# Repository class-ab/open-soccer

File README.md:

contains all the PCBs, code and general shared documentation used in the creation of Mindstormers' open soccer robot/s (2026+)

CAD: https://cad.onshape.com/documents/fc0a5e085ca7f56b4458a98d/w/3d7a112d05c35eb898b84bfe/e/c55f60db607fb82f3faf3afa?renderMode=0&uiState=6a391f8bb5ef6c9da8a4baea

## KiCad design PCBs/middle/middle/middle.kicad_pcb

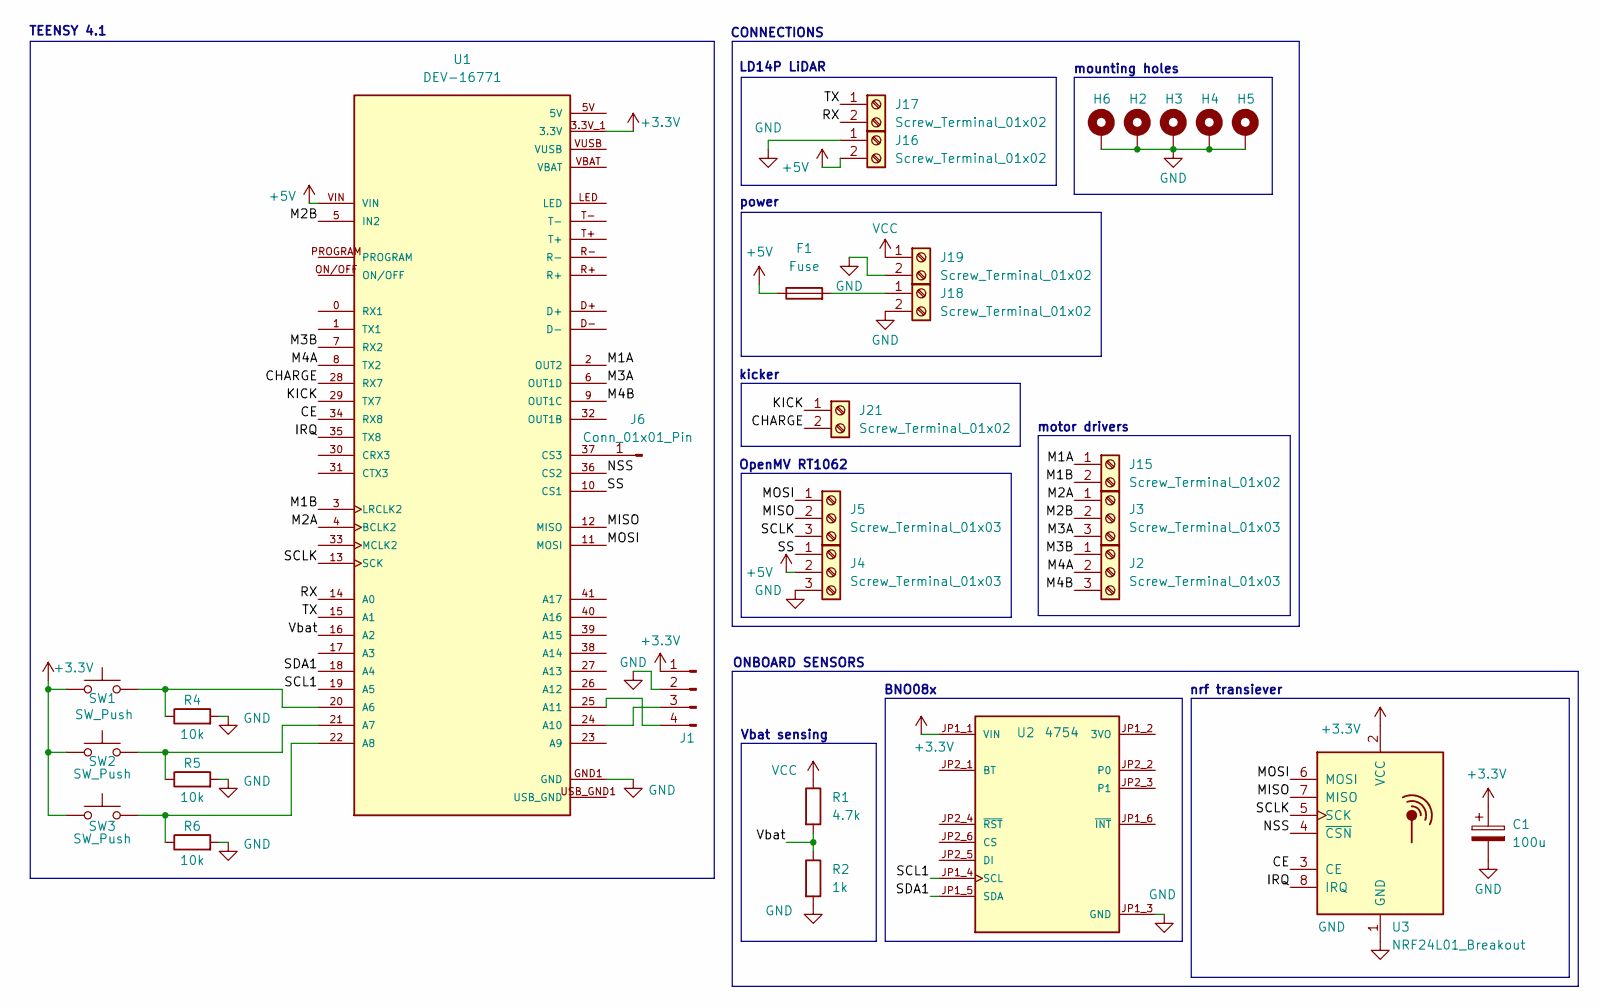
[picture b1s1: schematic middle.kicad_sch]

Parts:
C1: 100u; CP_Radial_D6.3mm_P2.50mm
F1: Fuse; Fuseholder_Clip-5x20mm_Littelfuse_520_Inline_P20.50x5.80mm_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
H2, H3, H4, H5, H6: MountingHole_Pad; MountingHole_3.2mm_M3_DIN965_Pad
J1: Conn_01x04_Pin; PinSocket_1x04_P2.54mm_Vertical
J2, J3, J4, J5: Screw_Terminal_01x03; TerminalBlock_Phoenix_MKDS-1,5-3_1x03_P5.00mm_Horizontal
J6: Conn_01x01_Pin; PinHeader_1x01_P2.54mm_Vertical
J15, J16, J17, J18, J19, J21: Screw_Terminal_01x02; TerminalBlock_Phoenix_MKDS-1,5-2_1x02_P5.00mm_Horizontal
R1: 4.7k; R_Axial_DIN0207_L6.3mm_D2.5mm_P10.16mm_Horizontal
R2: 1k; R_Axial_DIN0207_L6.3mm_D2.5mm_P10.16mm_Horizontal
R4, R5, R6: 10k; R_Axial_DIN0204_L3.6mm_D1.6mm_P5.08mm_Horizontal
SW1, SW2, SW3: SW_Push; SW_PUSH_6mm_H5mm
U1: DEV-16771; MODULE_DEV-16771; PARTREV 4.1
U2: 4754; MODULE_4754; PARTREV 2021-03-16
U3: NRF24L01_Breakout; nRF24L01_Breakout

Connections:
+3.3V: C1.1, J1.1, SW1.1, SW2.1, SW3.1, U1.3.3V_1 (3.3V), U1.3.3V_2 (3.3V), U1.3.3V_3 (3.3V), U2.JP1_1 (VIN), U3.2 (VCC)
+5V: F1.1, J4.2, J16.2, U1.VIN
/CE: U1.34 (RX8), U3.3 (CE)
/CHARGE: J21.2, U1.28 (RX7)
/IRQ: U1.35 (TX8), U3.8 (IRQ)
/KICK: J21.1, U1.29 (TX7)
/M1A: J15.1, U1.2 (OUT2)
/M1B: J15.2, U1.3 (LRCLK2)
/M2A: J3.1, U1.4 (BCLK2)
/M2B: J3.2, U1.5 (IN2)
/M3A: J3.3, U1.6 (OUT1D)
/M3B: J2.1, U1.7 (RX2)
/M4A: J2.2, U1.8 (TX2)
/M4B: J2.3, U1.9 (OUT1C)
/MISO: J5.2, U1.12 (MISO), U3.7 (MISO)
/MOSI: J5.1, U1.11 (MOSI), U3.6 (MOSI)
/NSS: U1.36 (CS2), U3.4 (~CSN)
/RX: J17.2, U1.14 (A0)
/SCL1: U1.19 (A5), U2.JP1_4 (SCL)
/SCLK: J5.3, U1.13 (SCK), U3.5 (SCK)
/SDA1: U1.18 (A4), U2.JP1_5 (SDA)
/SS: J4.1, U1.10 (CS1)
/TX: J17.1, U1.15 (A1)
/Vbat: R1.2, R2.1, U1.16 (A2)
GND: C1.2, H2.1 (1_1), H3.1 (1_1), H4.1 (1_1), H5.1 (1_1), H6.1 (1_1), J1.2, J4.3, J16.1, J18.2, J19.2, R2.2, R4.2, R5.2, R6.2, U1.GND1 (GND), U1.GND2 (GND), U1.GND3 (GND), U1.GND4 (GND), U1.GND5 (GND), U2.JP1_3 (GND), U3.1 (GND)
unnamed: J1.3, U1.24 (A10)
unnamed: J1.4, U1.25 (A11)
unnamed: J6.1 (Pin_1_1), U1.37 (CS3)
unnamed: F1.2, J18.1
unnamed: R4.1, SW1.2, U1.20 (A6)
unnamed: R5.1, SW2.2, U1.21 (A7)
unnamed: R6.1, SW3.2, U1.22 (A8)
USB_GND: U1.USB_GND1 (USB_GND), U1.USB_GND2 (USB_GND)
VCC: J19.1, R1.1

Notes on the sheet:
BNO08x
power
LD14P LiDAR
mounting holes
CONNECTIONS
OpenMV RT1062
nrf transiever
TEENSY 4.1
motor drivers
kicker
Vbat sensing
ONBOARD SENSORS

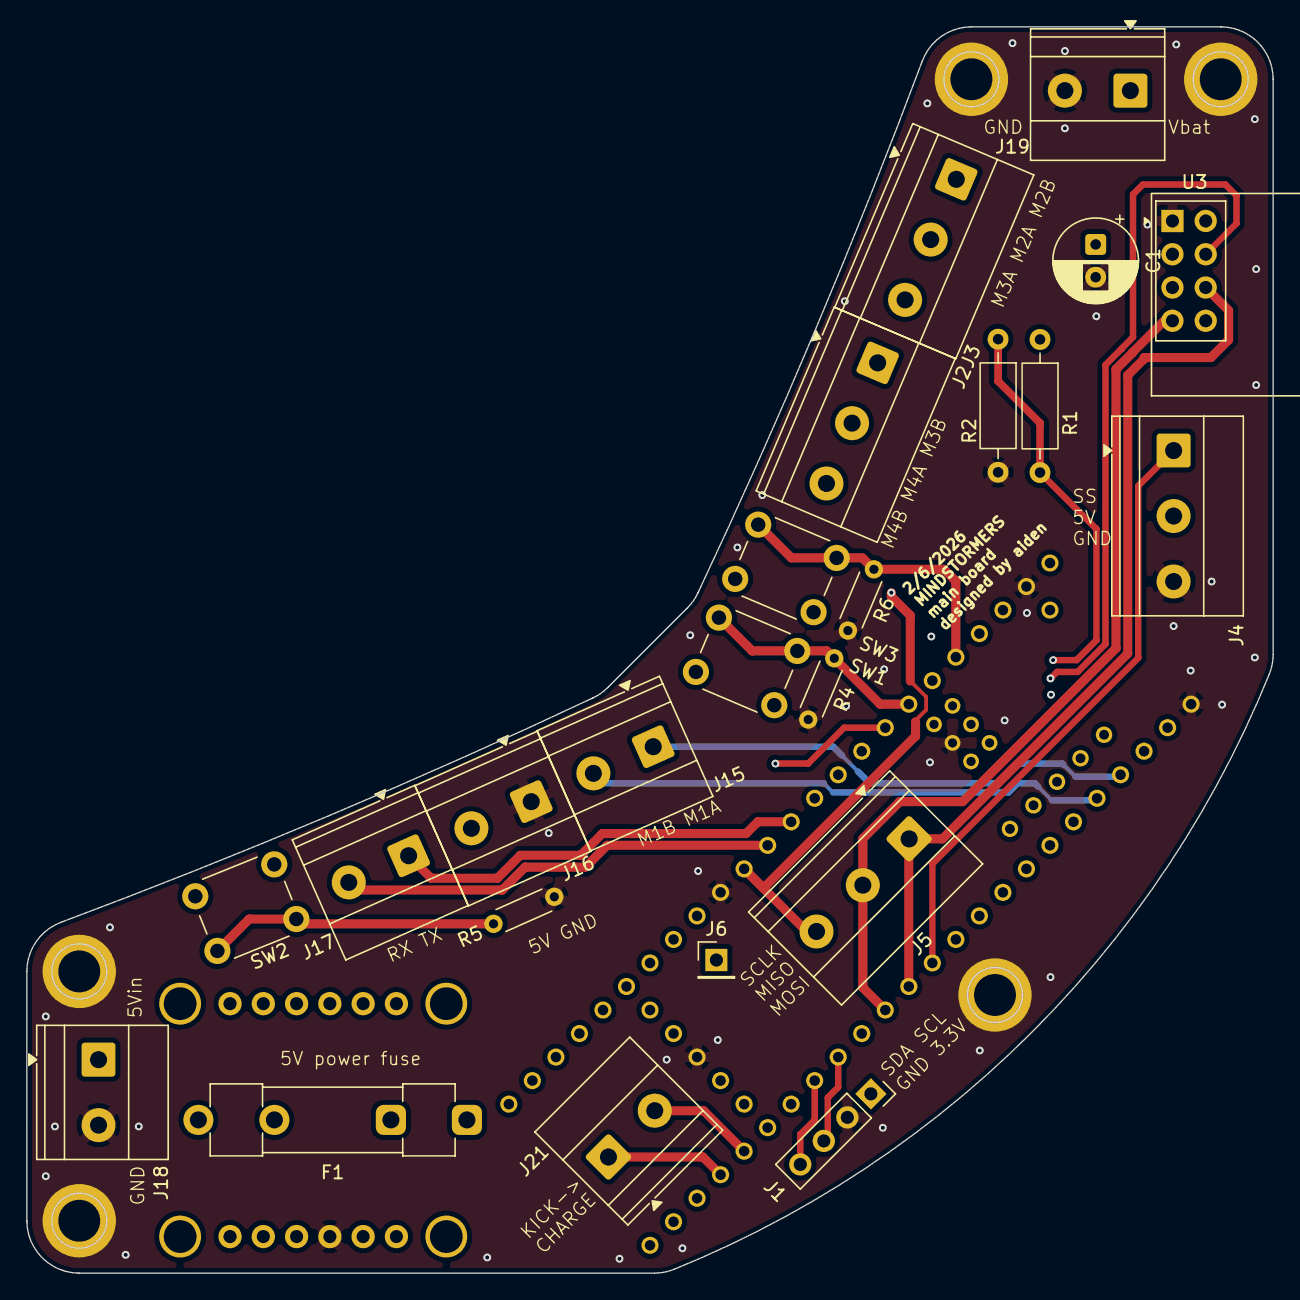
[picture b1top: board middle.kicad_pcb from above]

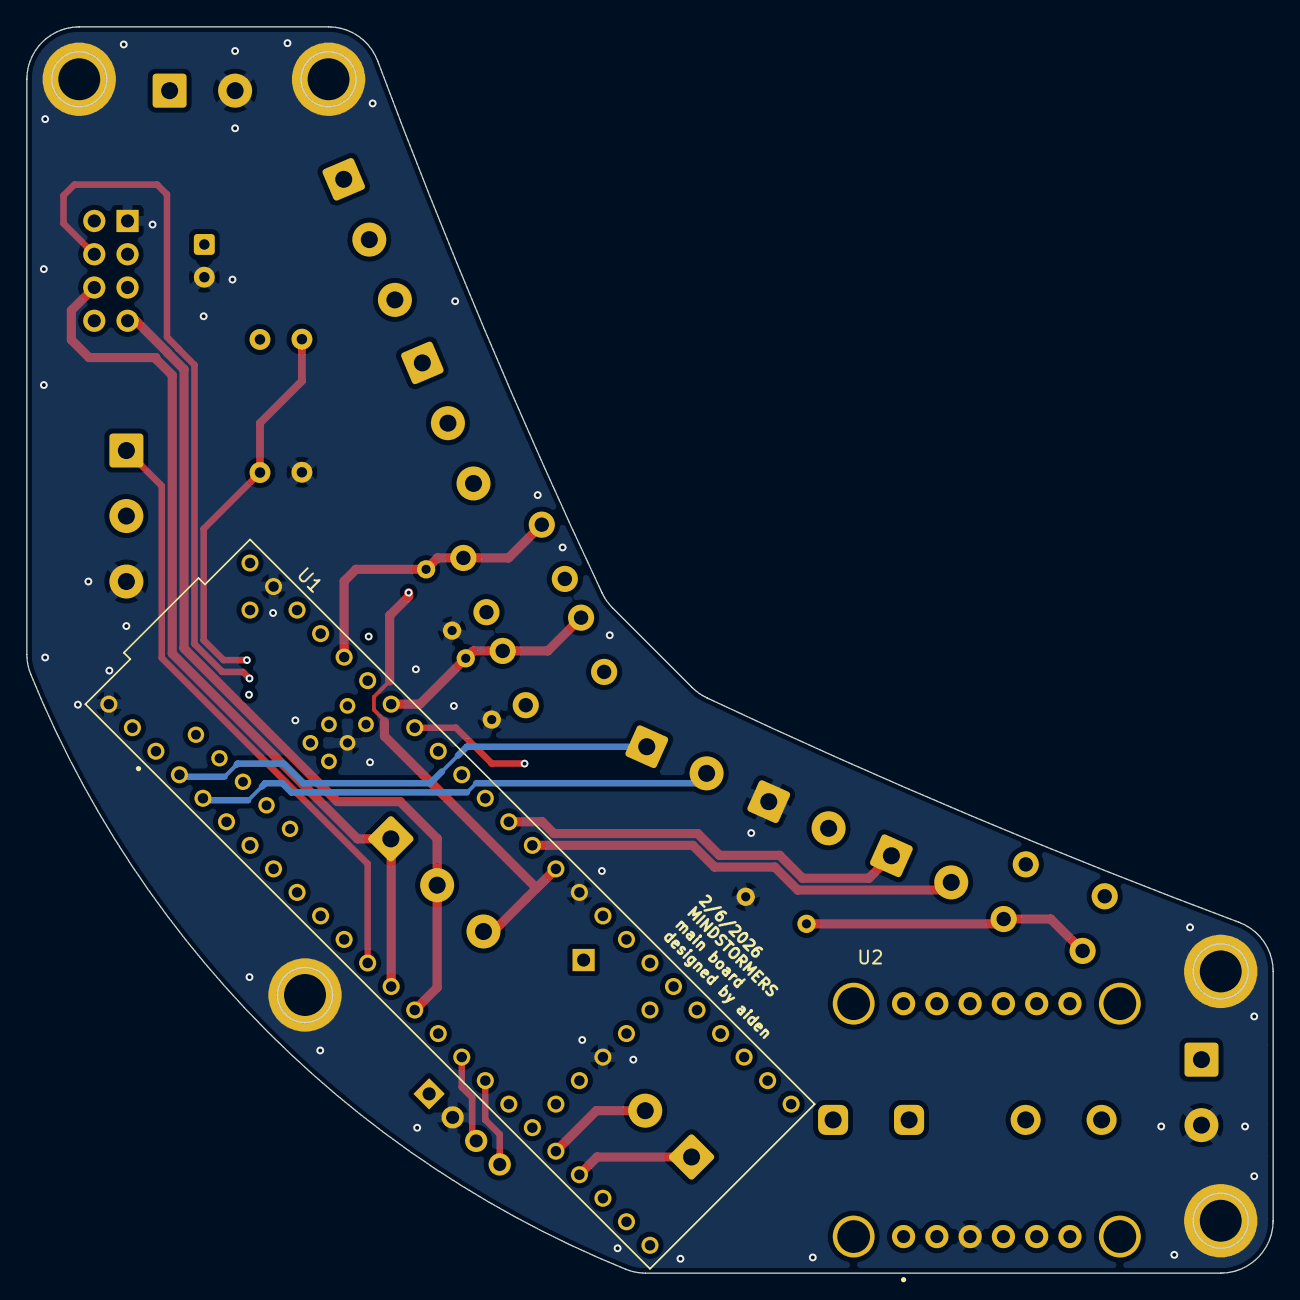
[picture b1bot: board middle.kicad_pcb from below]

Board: 4 copper layers, 95.1 x 95.1 mm, 30 parts (2 on the bottom side), 34 nets.

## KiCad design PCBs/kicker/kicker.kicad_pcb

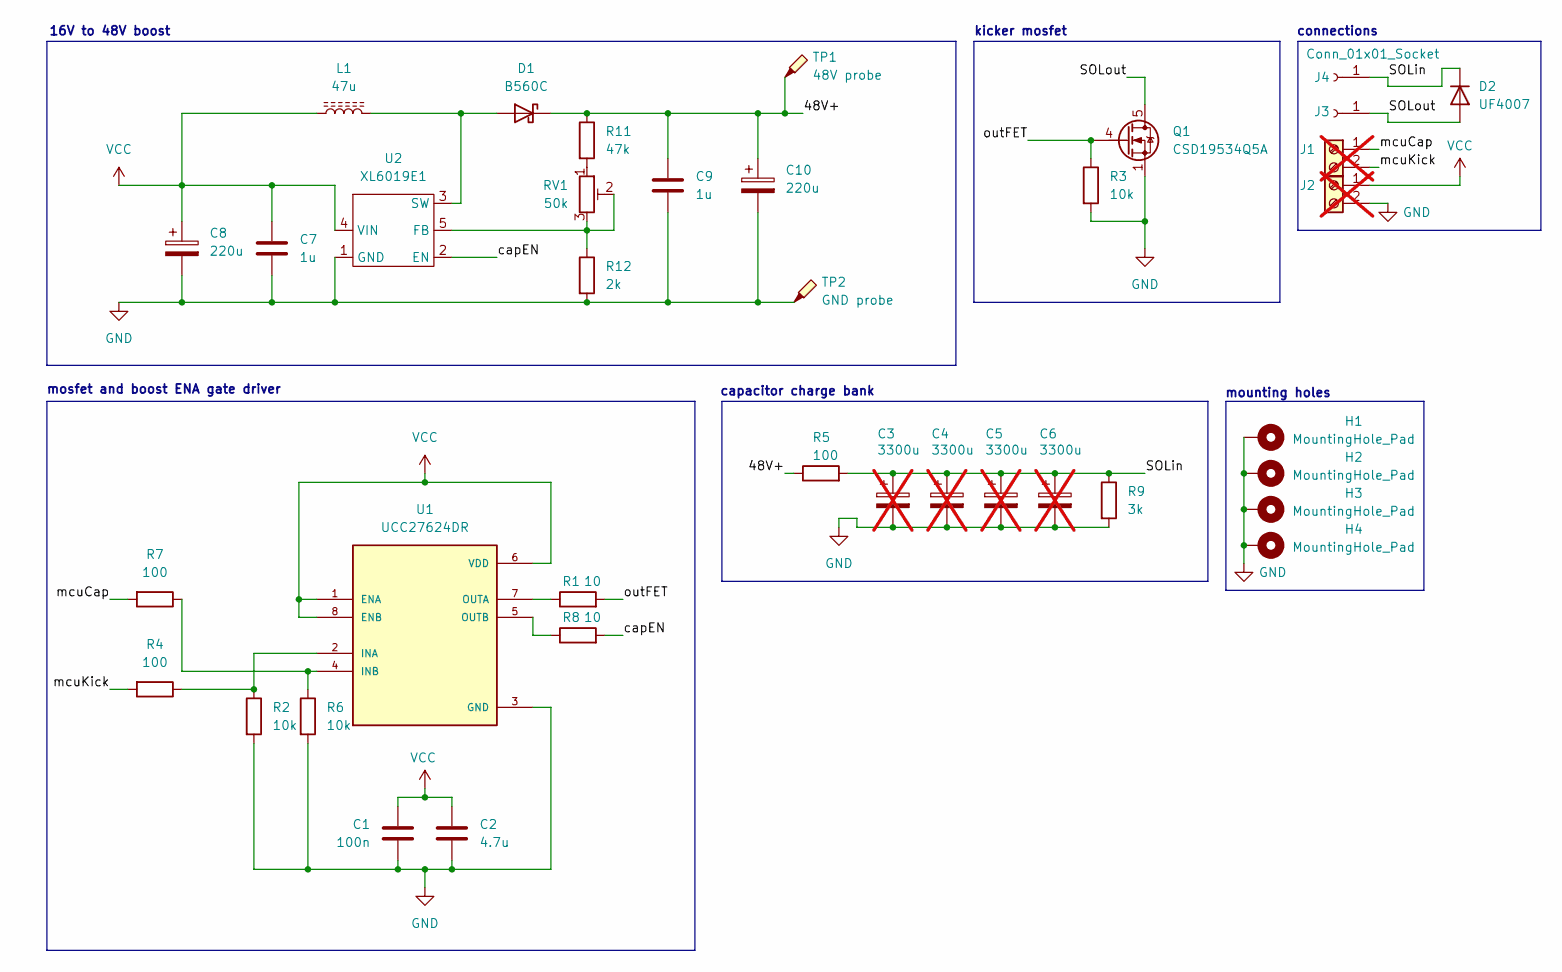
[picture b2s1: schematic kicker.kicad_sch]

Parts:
C1: 100n; C_1206_3216Metric
C2: 4.7u; C_1206_3216Metric
C3, C4, C5, C6: 3300u; CP_Radial_D18.0mm_P7.50mm; not fitted
C7, C9: 1u; C_1206_3216Metric
C8, C10: 220u; CP_Elec_10x10.5
D1: B560C; DO-214AB
D2: UF4007; D_DO-41_SOD81_P10.16mm_Horizontal
H1, H2, H3, H4: MountingHole_Pad; MountingHole_3.2mm_M3_DIN965_Pad
J1, J2: Screw_Terminal_01x02; TerminalBlock_Phoenix_MKDS-1,5-2_1x02_P5.00mm_Horizontal; not fitted
J3, J4: Conn_01x01_Socket; SolderWirePad_1x01_SMD_3x6mm
L1: 47u; L_Sunlord_MWSA1206S-470
Q1: CSD19534Q5A; TDSON-8-1
R1, R8: 10; R_0805_2012Metric
R2, R3, R6: 10k; R_0603_1608Metric
R4, R7: 100; R_0603_1608Metric
R5: 100; TO-263-2
R9: 3k; R_2512_6332Metric
R11: 47k; R_0603_1608Metric
R12: 2k; R_0603_1608Metric
RV1: 50k; Potentiometer_Bourns_3296W_Vertical
TP1: 48V probe; TestPoint_THTPad_1.5x1.5mm_Drill0.7mm
TP2: GND probe; TestPoint_THTPad_1.5x1.5mm_Drill0.7mm
U1: UCC27624DR; SOIC-8_3.9x4.9mm_P1.27mm; PARTREV B
U2: XL6019E1; TO-263-5_TabPin3

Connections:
/48V+: C9.1, C10.1, D1.1 (K), R5.1, R11.1, TP1.1 (1_1)
/SOLin: C3.1, C4.1, C5.1, C6.1, D2.1 (K), J4.1 (Pin_1_1), R5.2, R9.1
/SOLout: D2.2 (A), J3.1 (Pin_1_1), Q1.5 (D)
/capEN: R8.2, U2.2 (EN)
/mcuCap: J1.1, R7.2
/mcuKick: J1.2, R4.2
/outFET: Q1.4 (G), R1.2, R3.1
GND: C1.2, C2.2, C3.2, C4.2, C5.2, C6.2, C7.2, C8.2, C9.2, C10.2, H1.1 (1_1), H2.1 (1_1), H3.1 (1_1), H4.1 (1_1), J2.2, Q1.1 (S), Q1.2 (S), Q1.3 (S), R2.2, R3.2, R6.2, R9.2, R12.2, TP2.1 (1_1), U1.3 (GND), U2.1 (GND)
unnamed: D1.2 (A), L1.2, U2.3 (SW)
unnamed: R11.2, RV1.1
unnamed: R2.1, R4.1, U1.2 (INA)
unnamed: R6.1, R7.1, U1.4 (INB)
unnamed: R1.1, U1.7 (OUTA)
unnamed: R8.1, U1.5 (OUTB)
unnamed: R12.1, RV1.2, RV1.3, U2.5 (FB)
VCC: C1.1, C2.1, C7.1, C8.1, J2.1, L1.1, U1.1 (ENA), U1.6 (VDD), U1.8 (ENB), U2.4 (VIN)

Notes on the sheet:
connections
mosfet and boost ENA gate driver
capacitor charge bank
mounting holes
16V to 48V boost
kicker mosfet

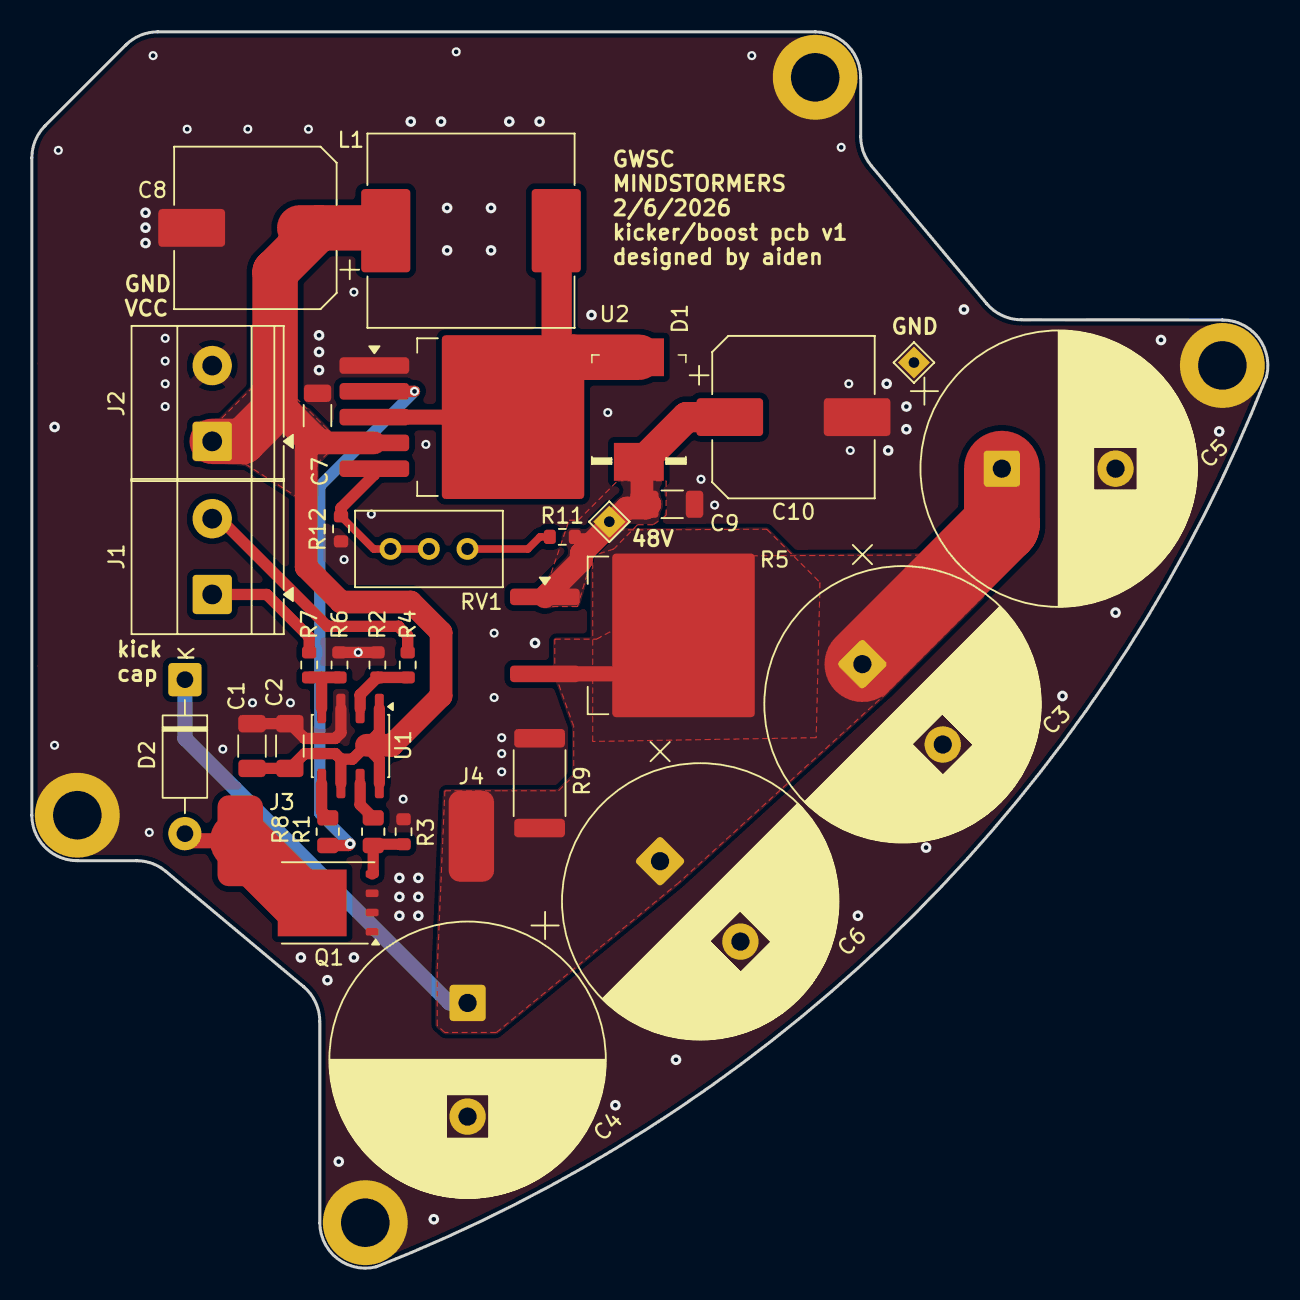
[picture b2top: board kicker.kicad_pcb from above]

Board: 2 copper layers, 81.5 x 81.6 mm, 38 parts (0 on the bottom side), 16 nets.

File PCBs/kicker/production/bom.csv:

Designator,Footprint,Quantity,Value,LCSC Part #
C1,1206,1,100n,
"C10, C8",CP_Elec_10x10.5,2,220u,
C2,1206,1,4.7u,
"C7, C9",1206,2,1u,
D1,DO-214AB,1,B560C,
D2,D_DO-41_SOD81_P10.16mm_Horizontal,1,UF4007,
"J3, J4",SolderWirePad_1x01_SMD_3x6mm,2,Conn_01x01_Socket,
L1,L_Sunlord_MWSA1206S-470,1,47u,
Q1,TDSON-8-1,1,CSD19534Q5A,
"R1, R8",0805,2,10,
R11,0603,1,47k,
R12,0603,1,2k,
"R2, R3, R6",0603,3,10k,
"R4, R7",0603,2,100,
R5,TO-263-2,1,100,
R9,2512,1,3k,
RV1,Potentiometer_Bourns_3296W_Vertical,1,50k,
TP1,TestPoint_THTPad_1.5x1.5mm_Drill0.7mm,1,48V probe,
TP2,TestPoint_THTPad_1.5x1.5mm_Drill0.7mm,1,GND probe,
U1,SOIC-8_3.9x4.9mm_P1.27mm,1,UCC27624DR,
U2,TO-263-5_TabPin3,1,XL6019E1,

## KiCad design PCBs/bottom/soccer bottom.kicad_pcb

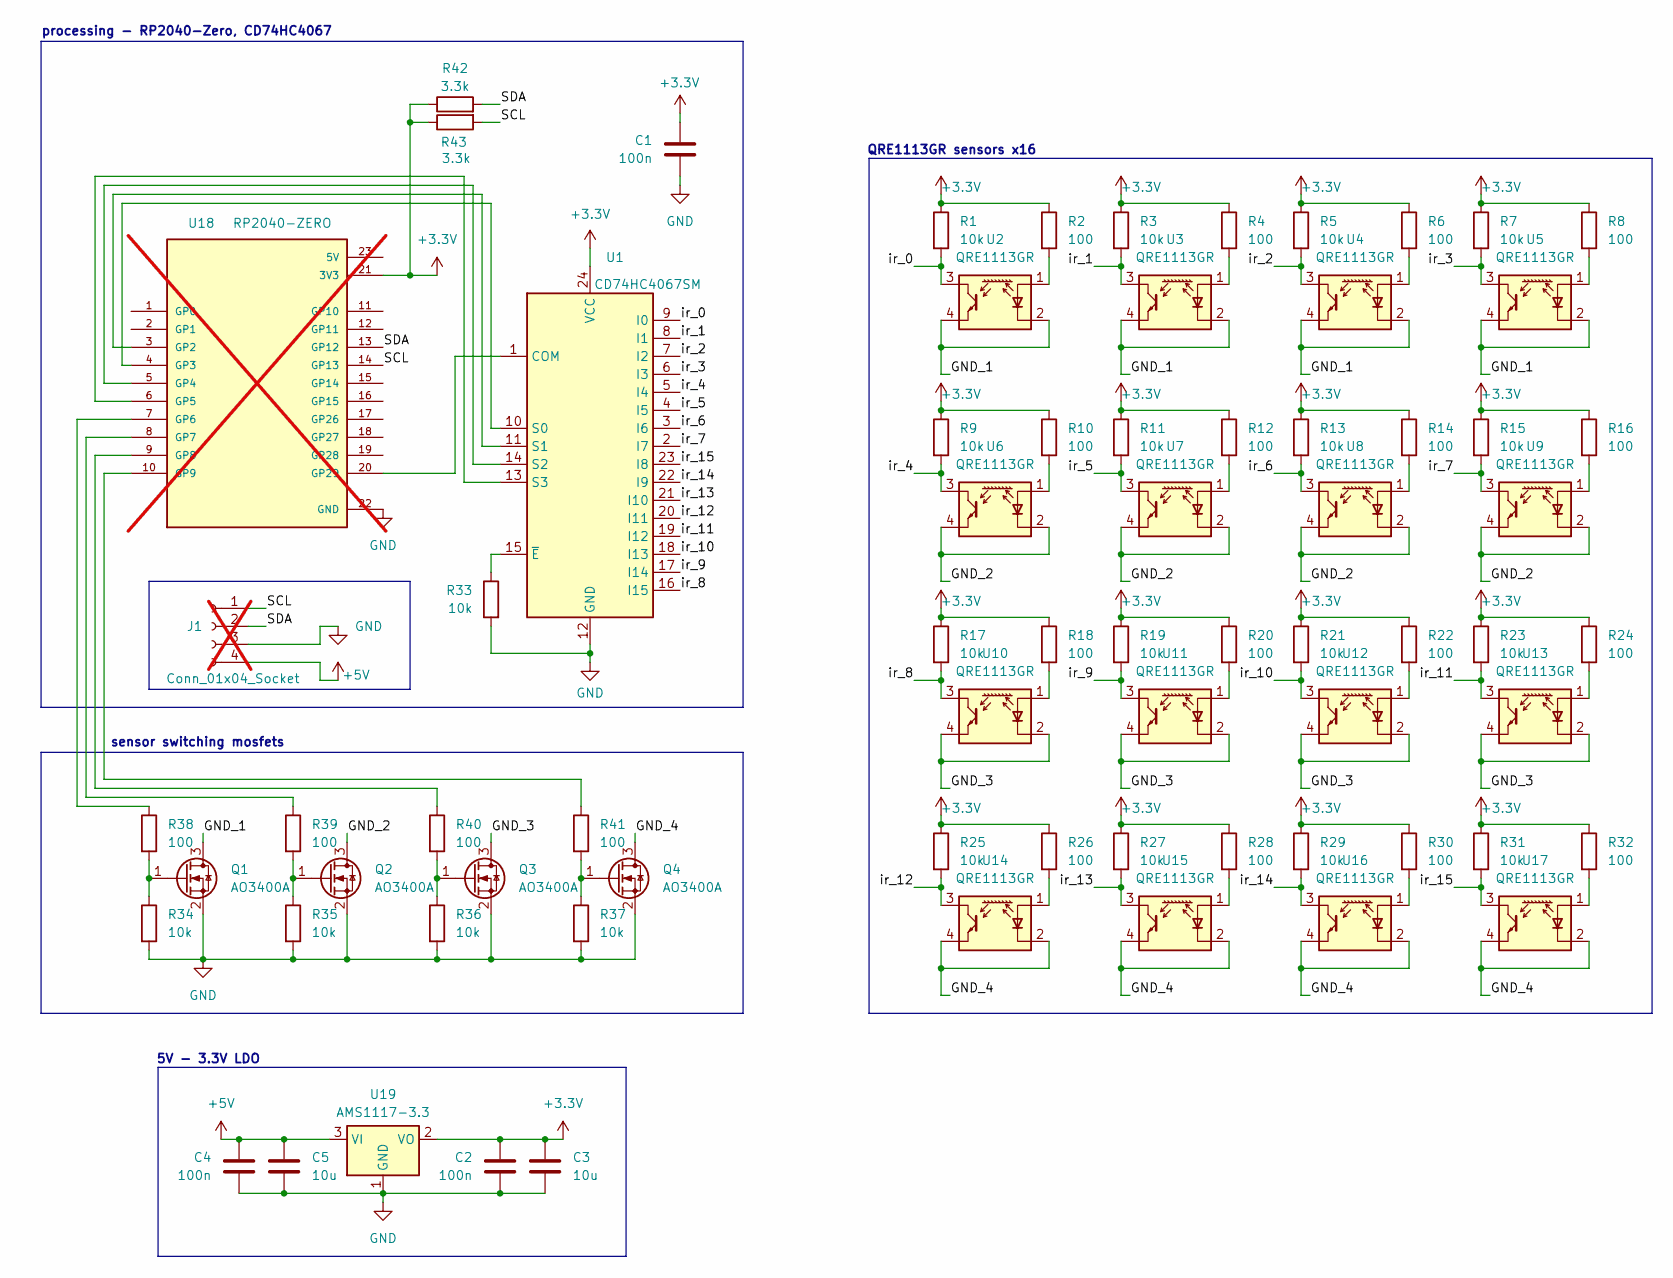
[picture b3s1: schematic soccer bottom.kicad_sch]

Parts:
C1, C2, C4: 100n; C_0805_2012Metric
C3, C5: 10u; C_0805_2012Metric
J1: Conn_01x04_Socket; JST_XH_B4B-XH-A_1x04_P2.50mm_Vertical; not fitted
Q1, Q2, Q3, Q4: AO3400A; SOT-23
R1, R3, R5, R7, R9, R11, R13, R15, R17, R19, R21, R23, R25, R27, R29, R31, R33, R34, R35, R36, R37: 10k; R_0805_2012Metric
R2, R4, R6, R8, R10, R12, R14, R16, R18, R20, R22, R24, R26, R28, R30, R32, R38, R39, R40, R41: 100; R_0805_2012Metric
R42, R43: 3.3k; R_0805_2012Metric
U1: CD74HC4067SM; SSOP-24_5.3x8.2mm_P0.65mm
U2, U3, U4, U5, U6, U7, U8, U9, U10, U11, U12, U13, U14, U15, U16, U17: QRE1113GR; OnSemi_CASE100CY
U18: RP2040-ZERO; MODULE_RP2040-ZERO; PARTREV NA; not fitted
U19: AMS1117-3.3; SOT-223-3_TabPin2

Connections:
+3.3V: C1.1, C2.1, C3.1, R1.1, R2.1, R3.1, R4.1, R5.1, R6.1, R7.1, R8.1, R9.1, R10.1, R11.1, R12.1, R13.1, R14.1, R15.1, R16.1, R17.1, R18.1, R19.1, R20.1, R21.1, R22.1, R23.1, R24.1, R25.1, R26.1, R27.1, R28.1, R29.1, R30.1, R31.1, R32.1, R42.1, R43.1, U1.24 (VCC), U18.21 (3V3), U19.2 (VO)
+5V: C4.1, C5.1, J1.4, U19.3 (VI)
/GND_1: Q1.3 (D), U2.2 (K), U2.4, U3.2 (K), U3.4, U4.2 (K), U4.4, U5.2 (K), U5.4
/GND_2: Q2.3 (D), U6.2 (K), U6.4, U7.2 (K), U7.4, U8.2 (K), U8.4, U9.2 (K), U9.4
/GND_3: Q3.3 (D), U10.2 (K), U10.4, U11.2 (K), U11.4, U12.2 (K), U12.4, U13.2 (K), U13.4
/GND_4: Q4.3 (D), U14.2 (K), U14.4, U15.2 (K), U15.4, U16.2 (K), U16.4, U17.2 (K), U17.4
/SCL: J1.1, R43.2, U18.14 (GP13)
/SDA: J1.2, R42.2, U18.13 (GP12)
/ir_0: R1.2, U1.9 (I0), U2.3
/ir_1: R3.2, U1.8 (I1), U3.3
/ir_2: R5.2, U1.7 (I2), U4.3
/ir_3: R7.2, U1.6 (I3), U5.3
/ir_4: R9.2, U1.5 (I4), U6.3
/ir_5: R11.2, U1.4 (I5), U7.3
/ir_6: R13.2, U1.3 (I6), U8.3
/ir_7: R15.2, U1.2 (I7), U9.3
/ir_8: R17.2, U1.16 (I15), U10.3
/ir_9: R19.2, U1.17 (I14), U11.3
/ir_10: R21.2, U1.18 (I13), U12.3
/ir_11: R23.2, U1.19 (I12), U13.3
/ir_12: R25.2, U1.20 (I11), U14.3
/ir_13: R27.2, U1.21 (I10), U15.3
/ir_14: R29.2, U1.22 (I9), U16.3
/ir_15: R31.2, U1.23 (I8), U17.3
GND: C1.2, C2.2, C3.2, C4.2, C5.2, J1.3, Q1.2 (S), Q2.2 (S), Q3.2 (S), Q4.2 (S), R33.2, R34.2, R35.2, R36.2, R37.2, U1.12 (GND), U18.22 (GND), U19.1 (GND)
unnamed: Q1.1 (G), R34.1, R38.2
unnamed: Q2.1 (G), R35.1, R39.2
unnamed: Q3.1 (G), R36.1, R40.2
unnamed: Q4.1 (G), R37.1, R41.2
unnamed: U1.1 (COM), U18.20 (GP29)
unnamed: U1.10 (S0), U18.4 (GP3)
unnamed: U1.11 (S1), U18.3 (GP2)
unnamed: U1.14 (S2), U18.5 (GP4)
unnamed: U1.13 (S3), U18.6 (GP5)
unnamed: R33.1, U1.15 (~E)
unnamed: R2.2, U2.1 (A)
unnamed: R4.2, U3.1 (A)
unnamed: R6.2, U4.1 (A)
unnamed: R8.2, U5.1 (A)
unnamed: R10.2, U6.1 (A)
unnamed: R12.2, U7.1 (A)
unnamed: R14.2, U8.1 (A)
unnamed: R16.2, U9.1 (A)
unnamed: R18.2, U10.1 (A)
unnamed: R20.2, U11.1 (A)
unnamed: R22.2, U12.1 (A)
unnamed: R24.2, U13.1 (A)
unnamed: R26.2, U14.1 (A)
unnamed: R28.2, U15.1 (A)
unnamed: R30.2, U16.1 (A)
unnamed: R32.2, U17.1 (A)
unnamed: R38.1, U18.7 (GP6)
unnamed: R39.1, U18.8 (GP7)
unnamed: R40.1, U18.9 (GP8)
unnamed: R41.1, U18.10 (GP9)

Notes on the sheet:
5V - 3.3V LDO
QRE1113GR sensors x16
processing - RP2040-Zero, CD74HC4067
sensor switching mosfets

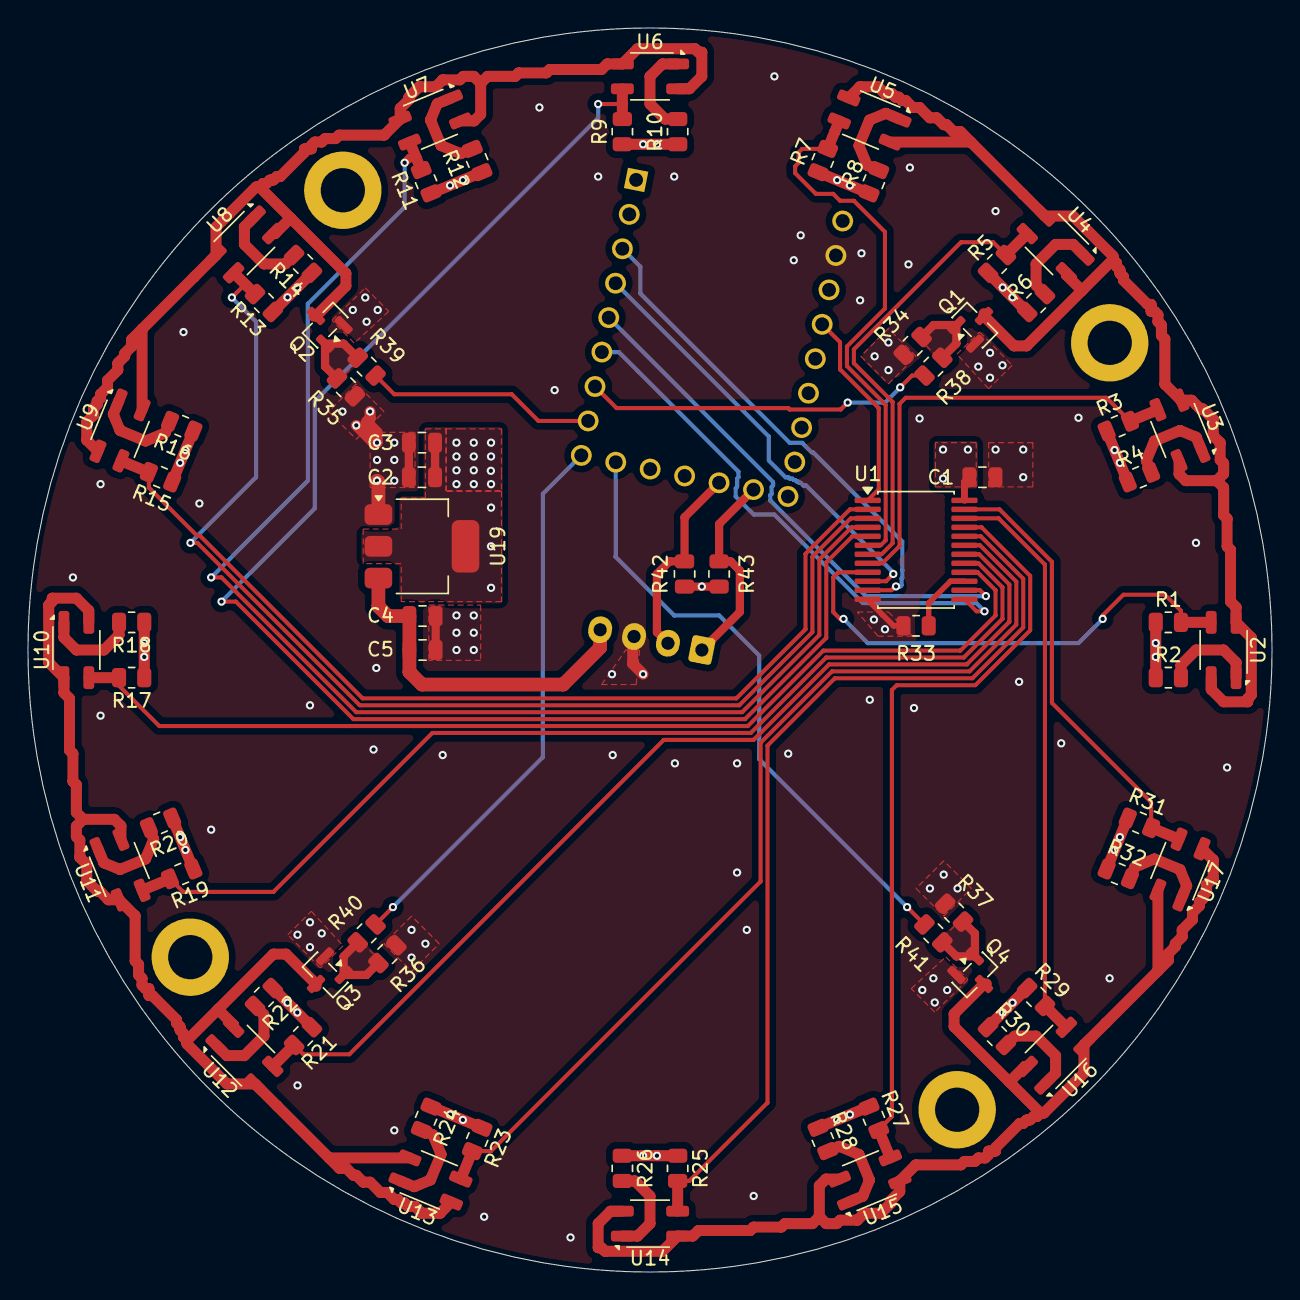
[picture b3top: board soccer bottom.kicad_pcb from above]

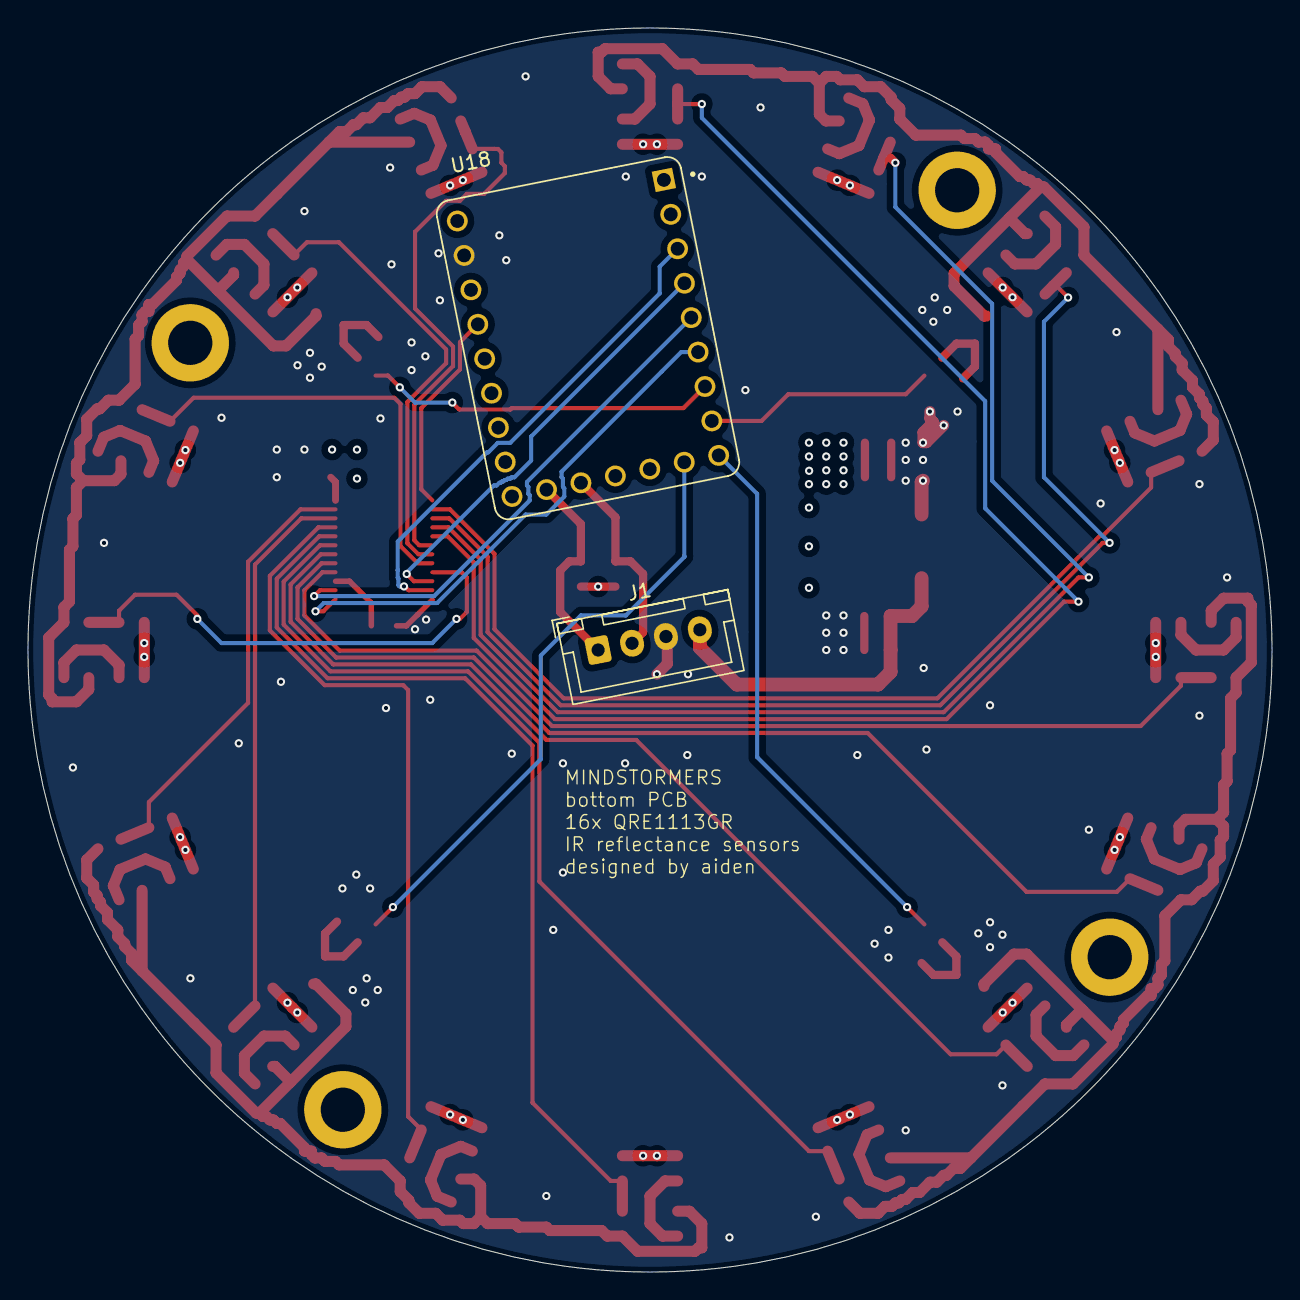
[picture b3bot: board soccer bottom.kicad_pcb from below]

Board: 4 copper layers, 90.0 x 90.0 mm, 72 parts (2 on the bottom side), 55 nets.

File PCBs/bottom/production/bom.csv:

Designator,Footprint,Quantity,Value,LCSC Part #
"C1, C2, C4",0805,3,100n,
"C3, C5",0805,2,10u,
"Q1, Q2, Q3, Q4",SOT-23,4,AO3400A,
"R1, R11, R13, R15, R17, R19, R21, R23, R25, R27, R29, R3, R31, R33, R34, R35, R36, R37, R5, R7, R9",0805,21,10k,
"R10, R12, R14, R16, R18, R2, R20, R22, R24, R26, R28, R30, R32, R38, R39, R4, R40, R41, R6, R8",0805,20,100,
"R42, R43",0805,2,3.3k,
U1,SSOP-24_5.3x8.2mm_P0.65mm,1,CD74HC4067SM,
"U10, U11, U12, U13, U14, U15, U16, U17, U2, U3, U4, U5, U6, U7, U8, U9",OnSemi_CASE100CY,16,QRE1113GR,
U19,SOT-223-3_TabPin2,1,AMS1117-3.3,

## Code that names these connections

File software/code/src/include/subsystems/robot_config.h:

#pragma once

// On real hardware (ARDUINO) each binary controls exactly one robot, so these
// expand to nothing. The simulator runs multiple robot instances as separate
// threads and defines ARDUINO nowhere, so SIM_TLS/SIM_STATIC_TLS give each
// thread its own isolated copy of otherwise-shared firmware state.
#if defined(ARDUINO)
#include <Arduino.h>
#define SIM_TLS
#define SIM_STATIC_TLS static
#else
#define SIM_TLS thread_local
#define SIM_STATIC_TLS thread_local
#endif

// SPEED LIMITS
// Speed and acceleration limits are passed per move()/moveTo() call (strategy.cpp).
// Calibrate against measured full-command robot speed on the actual field.
constexpr float ROBOT_LINEAR_SPEED_MM_S = 3600.0f;

// Smallest normalized wheel command that reliably turns the wheels (motor
// deadband). Raise if the robot stalls near targets, lower if it creeps/hunts.
constexpr float MOTOR_MIN_COMMAND = 0.20f;

// ACCELERATION LIMITS (normalized units per second). Rotation must be fast:
// a slow output slew behind the heading loop makes it overshoot and oscillate.
constexpr float ACCEL_LIMIT = 2.0f;
constexpr float ROTATION_ACCEL_LIMIT = 0.65f;

// moveTo() position-to-speed proportional gain (normalized speed / mm).
// Reaches full speed at ~600 mm; the old 0.00065 gave sub-deadband commands
// below ~250 mm so the robot stalled short of targets.
constexpr float POSITION_KP = 0.0016f;
constexpr float POSITION_TOLERANCE_MM = 20.0f;
constexpr float HEADING_TOLERANCE_DEG = 5.0f;

// Heading PID output is normalized rotation command. D is d(error)/dt per IMU sample.
// KP saturates ROTATION_MAX_SPEED at ~65 deg error.
constexpr float HEADING_KP = 0.005f;
constexpr float HEADING_KI = 0.0f;
constexpr float HEADING_KD = 0.001f;
// Integral is accumulated in degree-seconds and clamped before applying KI.
constexpr float HEADING_INTEGRAL_MAX = 0.20f;
constexpr float YAW_SIGN = 1.0f;

// Tuning order: if heading oscillates lower HEADING_KP or raise HEADING_KD;
// if it is sluggish raise HEADING_KP. If translation overshoots lower
// POSITION_KP; if it is sluggish raise POSITION_KP or ACCEL_LIMIT.

// ball sensing
constexpr float CAMERA_MOUNT_OFFSET_DEG = 0.0f;
constexpr unsigned long BALL_DATA_TIMEOUT_MS = 300;
constexpr float BALL_TARGET_DISTANCE_CM = 15.0f;
constexpr float BALL_TARGET_ANGLE = 6.0f;

// #define DEBUG_MOVE
#define DEBUG_BALL_LINK
// #define DEBUG_LIDAR        // basic lidar info
// #define DEBUG_FIELDBALL    // requires DEBUG_LIDAR
// #define LOCAL_STATE
// #define LIDAR_POSE_STREAM  // advanced lidar debug + py script

// IMU
#define BNO08X_RESET -1

// motor pins
constexpr int M1a = 2; // FRONT LEFT
constexpr int M1b = 3;
constexpr int M2a = 5; // FRONT RIGHT
constexpr int M2b = 4;
constexpr int M3a = 9; // BACK LEFT
constexpr int M3b = 8;
constexpr int M4a = 7; // BACK RIGHT
constexpr int M4b = 6;

// dribbler ESC
constexpr int DRIBBLER_THROTTLE_PIN = 23;
constexpr int DRIBBLER_REVERSE_PIN = 17;
constexpr int DRIBBLER_PULSE_MIN = 1000;
constexpr int DRIBBLER_PULSE_NEUTRAL = 1500;
constexpr int DRIBBLER_PULSE_MAX = 2000;
constexpr int DRIBBLER_FORWARD_US = 2000;
constexpr int DRIBBLER_REVERSE_US = 1000;
constexpr int DRIBBLER_RUN_THROTTLE_US = 1200; // MAIN SPEED CHANGE THIS

// kicker pins
constexpr int kicker = 32;
constexpr int charge = 31;

// buttons
constexpr int button1 = A7;
constexpr int button2 = A6;
constexpr int button3 = A8;
constexpr unsigned long BUTTON_DEBOUNCE_MS = 30;

// OLED
constexpr int SCREEN_WIDTH = 128;
constexpr int SCREEN_HEIGHT = 64;
constexpr int OLED_RESET_PIN = -1;
constexpr uint8_t OLED_I2C_ADDRESS = 0x3C;
constexpr unsigned long DISPLAY_UPDATE_INTERVAL_MS = 250;  // each refresh blocks ~25 ms on I2C

// OpenMV 
#define BALL_UART      Serial7
#define BALL_UART_BAUD 115200
constexpr uint8_t BALL_PACKET_LEN = 8;
constexpr uint8_t BALL_SYNC = 0xAA;
constexpr uint8_t YELLOW_GOAL_SYNC = 0xAB; // not used currently
constexpr uint8_t BLUE_GOAL_SYNC = 0xAC; // not used currently

// LD14P LiDAR
#define LIDAR_UART      Serial3
#define LIDAR_UART_BAUD 230400
// LD14P motor speed PWM control loop (closed-loop on the reported scan speed).
constexpr uint8_t LIDAR_SPEED_CONTROL_PIN = 14;
constexpr uint32_t LIDAR_PWM_FREQUENCY_HZ = 1000;
// Start near the measured working duty; allow feedback to increase as needed
// to reach the target scan speed.
constexpr float LIDAR_PWM_ENTRY_DUTY_PERCENT = 78.0f;
constexpr float LIDAR_PWM_MIN_DUTY_PERCENT = 45.1f;
constexpr float LIDAR_PWM_MAX_DUTY_PERCENT = 100.0f;
constexpr float LIDAR_TARGET_SPEED_DEG_S = 2880.0f;
constexpr float LIDAR_SPEED_TOLERANCE_DEG_S = 36.0f;
constexpr unsigned long LIDAR_CONTROL_INTERVAL_MS = 125;

// battery
constexpr int BATTERY_PIN = A2;
constexpr float BATTERY_DIVIDER_R1 = 4700.0f;
constexpr float BATTERY_DIVIDER_R2 = 1000.0f;
constexpr float BATTERY_DIVIDER_RATIO =
  (BATTERY_DIVIDER_R1 + BATTERY_DIVIDER_R2) / BATTERY_DIVIDER_R2;

constexpr int ADC_RESOLUTION_BITS = 12;
constexpr int ADC_MAX_VALUE = (1 << ADC_RESOLUTION_BITS) - 1;
constexpr float ADC_REF_VOLTAGE = 3.3f;

constexpr float BATTERY_SHUTDOWN_VOLTAGE = 14.8f;
constexpr unsigned long BATTERY_CHECK_INTERVAL_MS = 5000;
constexpr int BATTERY_SAMPLE_COUNT = 3;

// motor calibration (currently unused)
constexpr float motorMult[5] = {
  1.0f,
  1.00f,
  1.00f,
  1.00f,
  1.00f
};

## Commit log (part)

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2026-02-19 test
2026-02-20 eeee
2026-02-20 v10 or smting
2026-02-20 20/2/26 test 1 final
2026-03-08 NEW MCU
    rp2040-zero and mosfets
    grr haven't made the pcb
    schematic is good tho!
2026-03-09 update parts list
2026-03-18 100k to 10k
2026-03-24 v2.1
2026-03-26 boost circuit v1
2026-03-30 delete
2026-03-30 kicker update
2026-03-31 kicad update?
2026-03-31 library fix desktop
2026-03-31 kicker actual start
2026-03-31 fix driver footprint
2026-04-01 kicker v0.1
2026-04-06 kicker schematic reorganise
2026-04-12 kicker board and outline
2026-04-13 kicker V1
2026-04-13 export v1
2026-04-14 bottom pcb update
2026-04-15 bottom v2 (pcb)
2026-04-18 kicker v2 review
2026-04-19 kicker v2
2026-04-19 kicker v2.1
2026-04-25 bottom align
2026-04-25 kicker fix
2026-05-03 middle pcb schematic
2026-05-03 middle v2
2026-05-05 kicker rotate diode
2026-05-07 middle revision
2026-05-08 mainboard layout
2026-05-11 middle BANANA board layout, wiring
2026-05-12 middle update
2026-05-23 main update
2026-05-25 nrf middle update 1 (NOT DONE)
2026-05-31 FINAL?
2026-05-31 final edit lol
2026-06-02 final
2026-06-02 pcb final final final?
2026-06-02 final v4 add esc to middle
2026-06-08 ORDERED PCBS
2026-06-16 software begin
2026-06-22 individual testing 22/6/26
2026-06-22 add CAD to README.md
